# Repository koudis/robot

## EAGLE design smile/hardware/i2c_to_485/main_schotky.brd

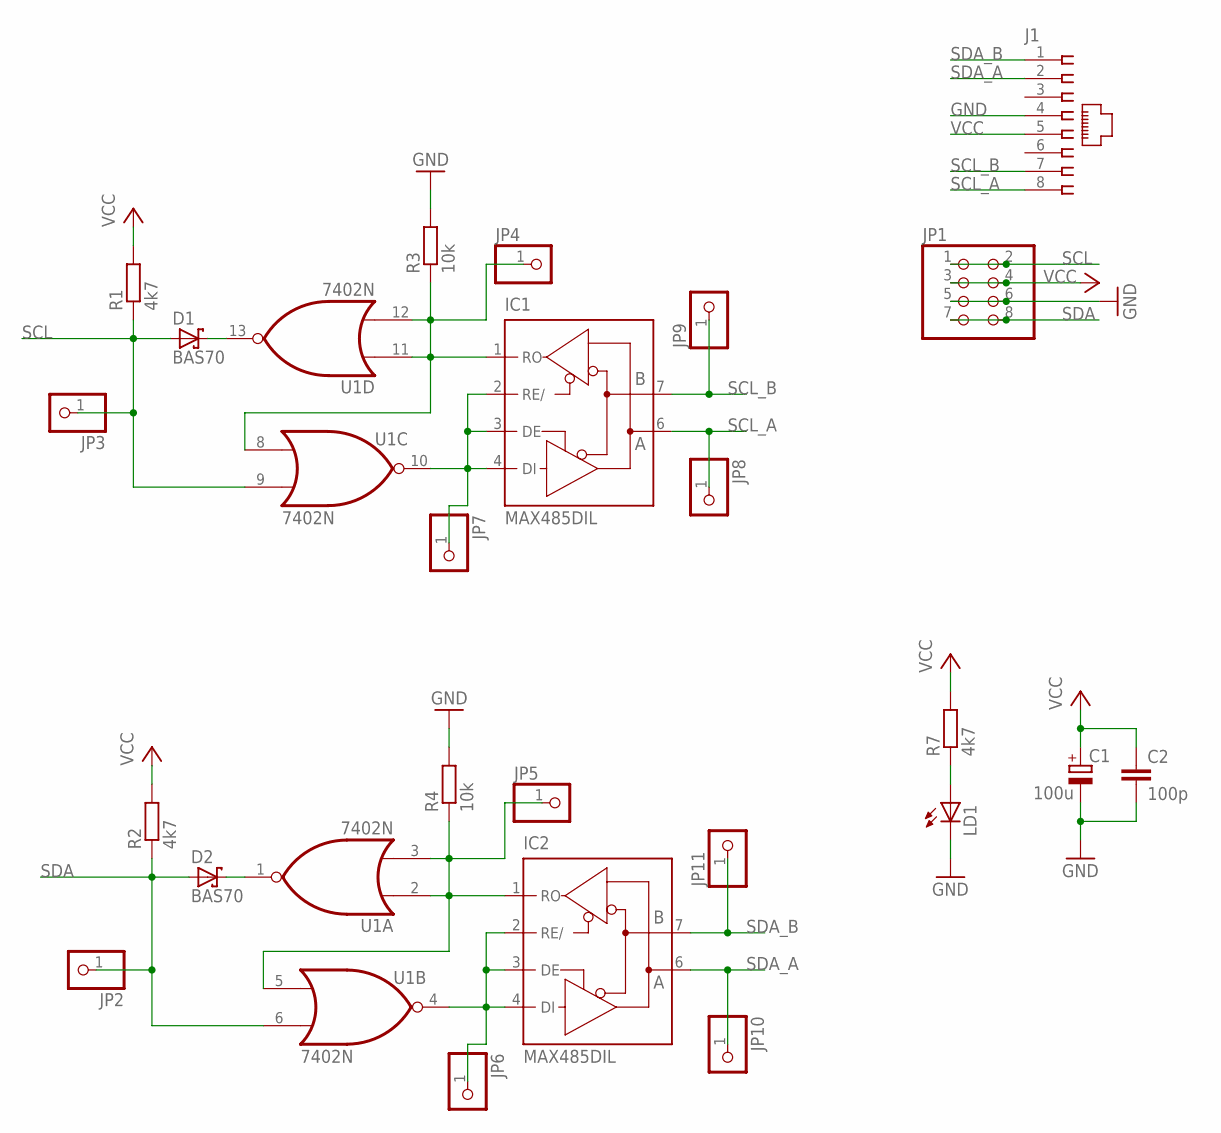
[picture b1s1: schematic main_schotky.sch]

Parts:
C1: 100u; E2-4
C2: 100p; C025-024X044
D1, D2: BAS70; SOT23
IC1, IC2: MAX485DIL; DIL08
J1: 215877-4
JP1: PINHD-2X4; 2X04
JP2, JP3, JP4, JP5, JP6, JP7, JP8, JP9, JP10, JP11: PINHD-1X1/LONG; 1X01
LD1: LEDSMT1206; 1206
R1, R2, R7: 4k7; R0805
R3, R4: 10k; R0805
U1: 7402N; DIL14

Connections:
GND: C1.-, C2.2, IC1.5 (GND), IC2.5 (GND), J1.4, JP1.5, JP1.6, LD1.C, R3.2, R4.2, U1.7 (GND)
unnamed: IC2.2 (RE/), IC2.3 (DE), IC2.4 (DI), JP6.1, U1.4 (O)
unnamed: IC2.1 (RO), JP5.1, R4.1, U1.2 (I0), U1.3 (I1), U1.5 (I0)
unnamed: D1.3 (C), U1.13 (O)
unnamed: D2.3 (C), U1.1 (O)
unnamed: LD1.A, R7.1
unnamed: IC1.2 (RE/), IC1.3 (DE), IC1.4 (DI), JP7.1, U1.10 (O)
unnamed: IC1.1 (RO), JP4.1, R3.1, U1.8 (I0), U1.11 (I0), U1.12 (I1)
SCL: D1.1 (A), JP1.1, JP1.2, JP3.1, R1.1, U1.9 (I1)
SCL_A: IC1.6 (A), J1.8, JP8.1
SCL_B: IC1.7 (B), J1.7, JP9.1
SDA: D2.1 (A), JP1.7, JP1.8, JP2.1, R2.1, U1.6 (I1)
SDA_A: IC2.6 (A), J1.2, JP10.1
SDA_B: IC2.7 (B), J1.1, JP11.1
VCC: C1.+, C2.1, IC1.8 (VCC), IC2.8 (VCC), J1.5, JP1.3, JP1.4, R1.2, R2.2, R7.2, U1.14 (VCC)

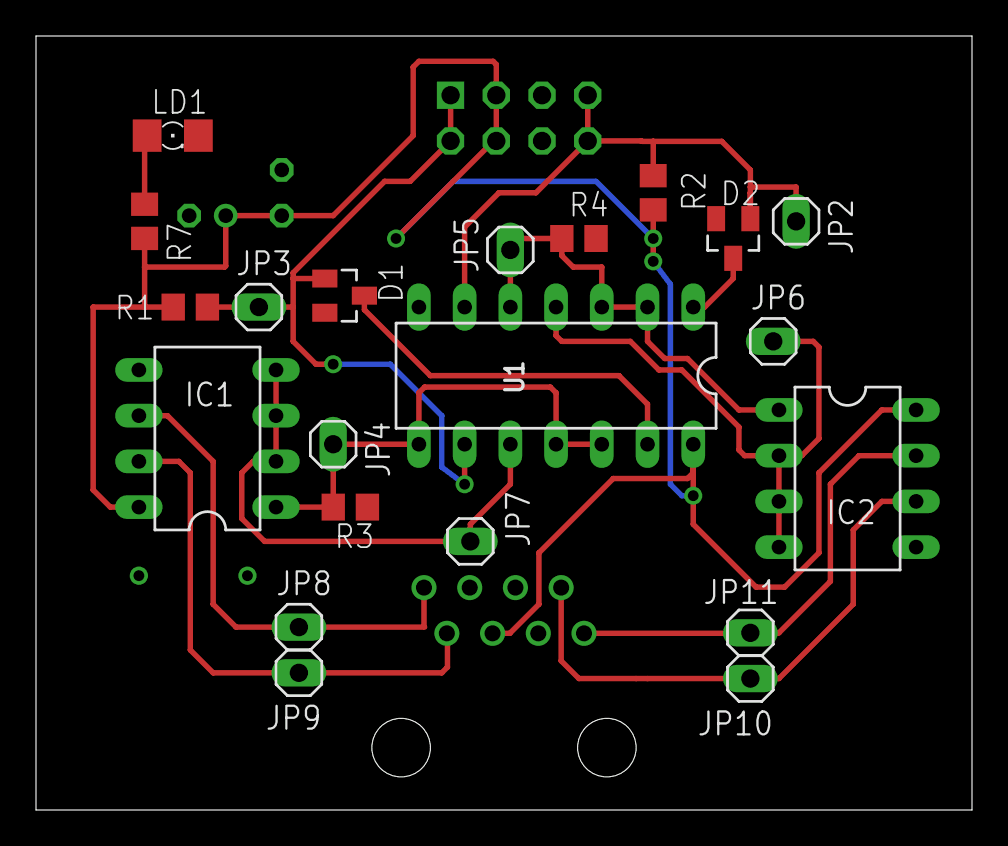
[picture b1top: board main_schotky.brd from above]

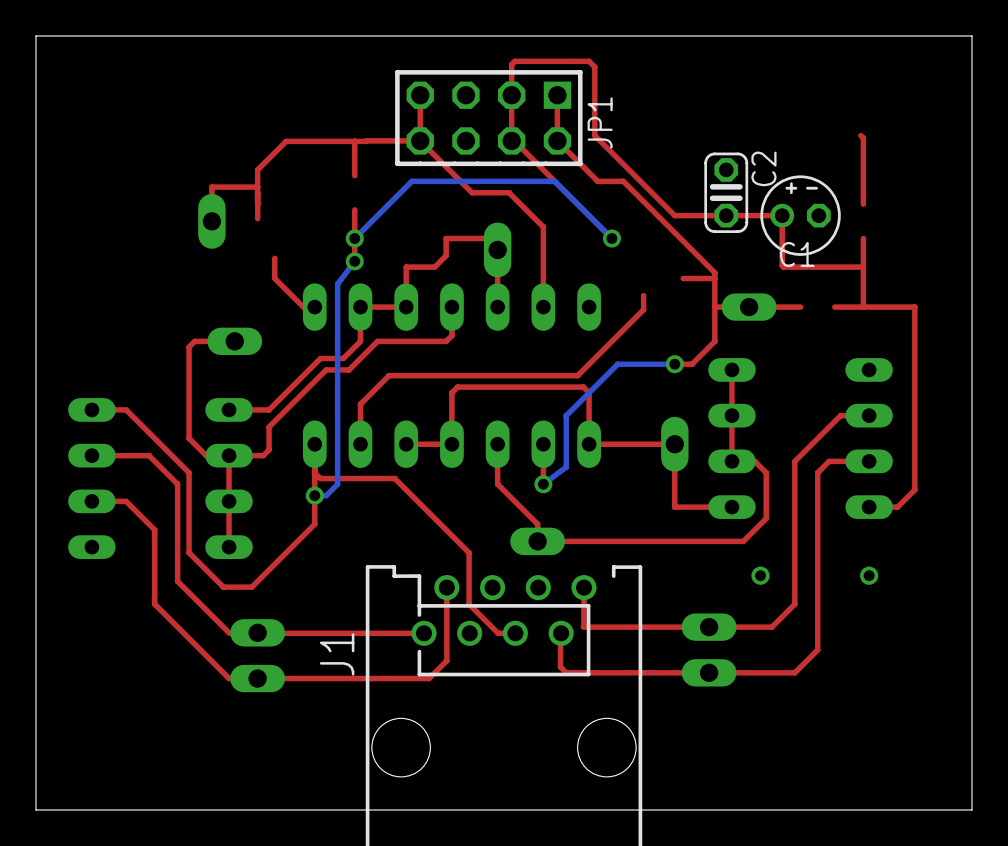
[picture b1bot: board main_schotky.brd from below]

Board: 2 copper layers, 52.0 x 43.0 mm, 25 parts (4 on the bottom side), 15 nets.

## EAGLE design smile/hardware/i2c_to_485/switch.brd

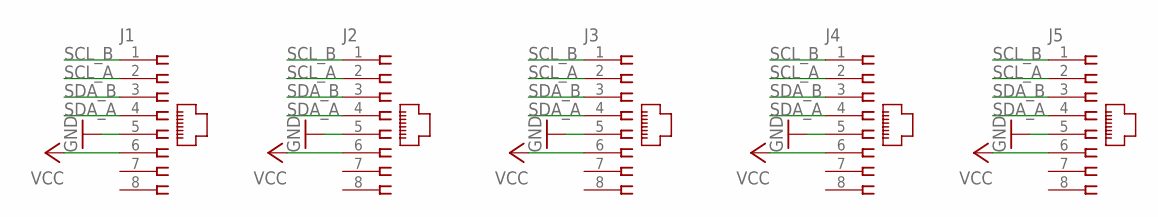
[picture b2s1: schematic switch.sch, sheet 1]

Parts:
J1, J2, J3, J4, J5: 215877-4

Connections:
GND: J1.5, J2.5, J3.5, J4.5, J5.5
SCL_A: J1.2, J2.2, J3.2, J4.2, J5.2
SCL_B: J1.1, J2.1, J3.1, J4.1, J5.1
SDA_A: J1.4, J2.4, J3.4, J4.4, J5.4
SDA_B: J1.3, J2.3, J3.3, J4.3, J5.3
VCC: J1.6, J2.6, J3.6, J4.6, J5.6

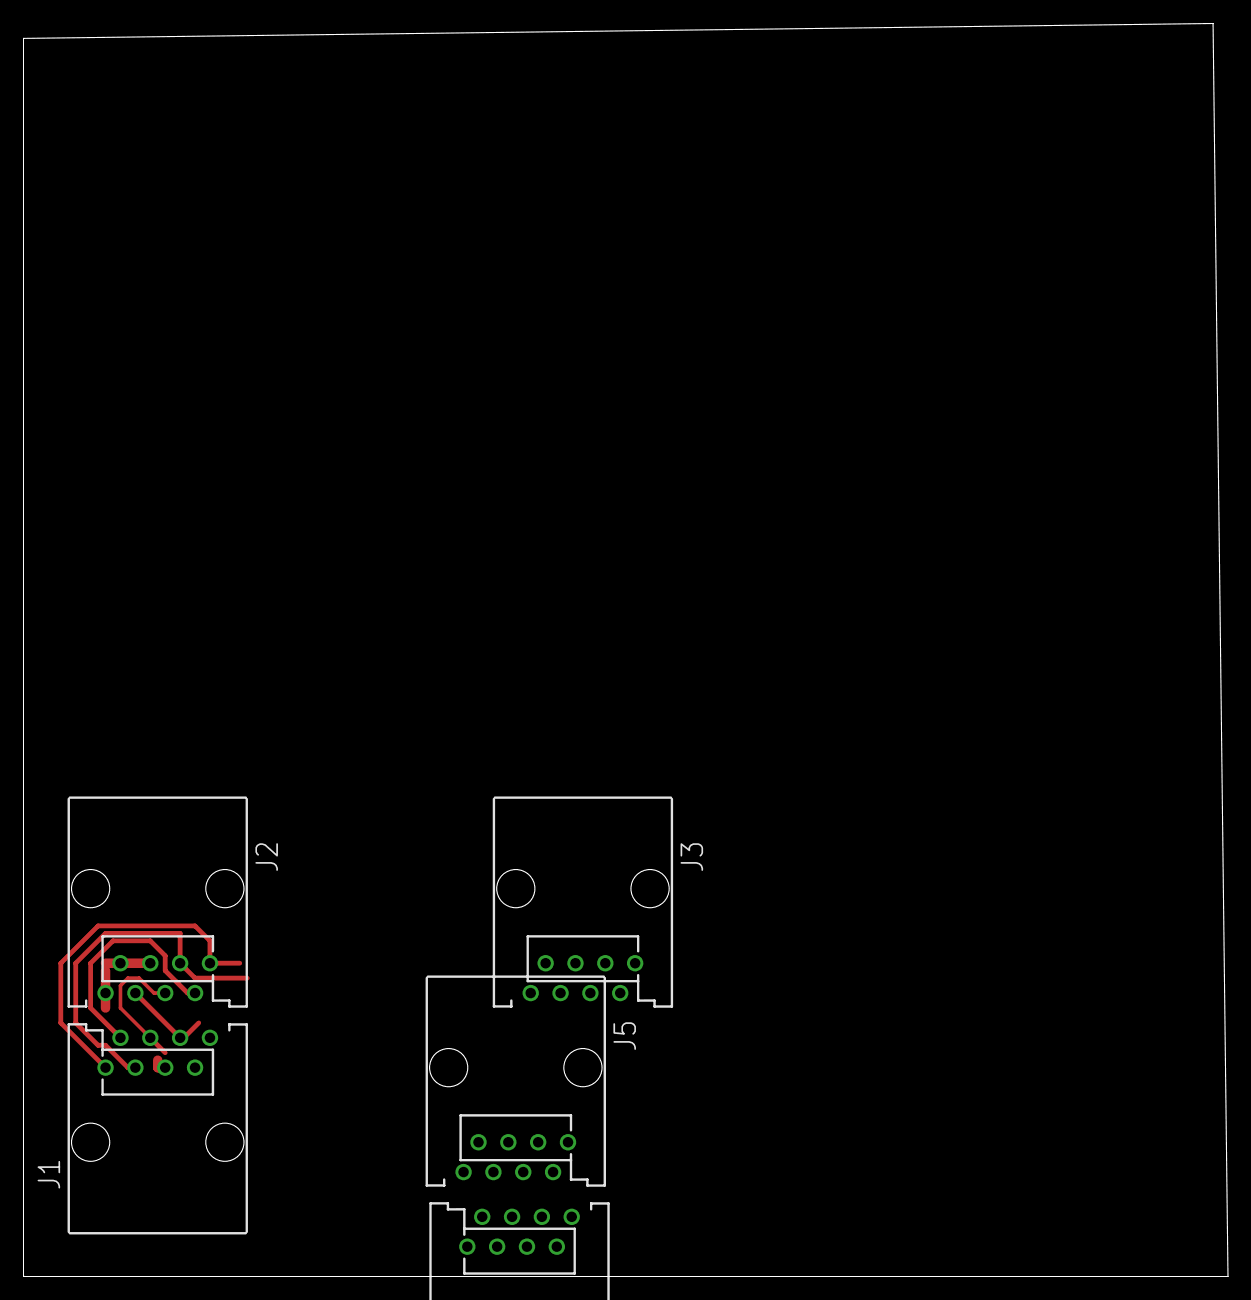
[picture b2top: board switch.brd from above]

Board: 2 copper layers, 102.5 x 106.7 mm, 5 parts (0 on the bottom side), 6 nets.

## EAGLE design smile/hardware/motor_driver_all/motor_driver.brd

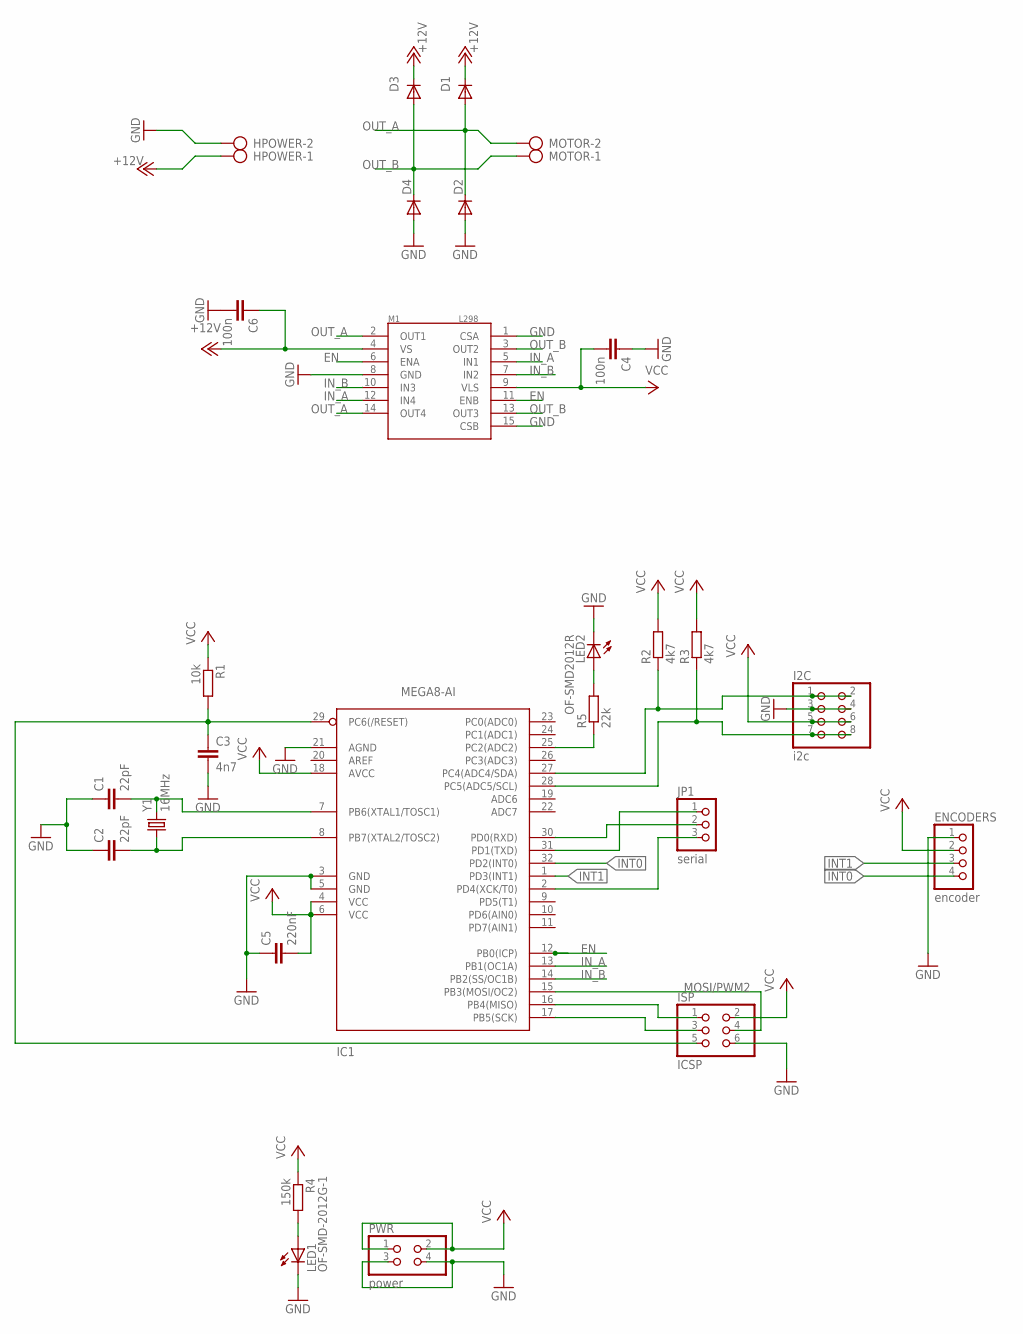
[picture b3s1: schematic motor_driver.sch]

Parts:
C1, C2: 22pF; C0805
C3: 4n7; 0805
C4: 100n; 0805
C5: 220nF; 0805
C6: 100n; C0805
D1, D2, D3, D4: DIODE-SMB; SMB
ENCODERS: encoder; 1X04-S
HPOWER: AK500/2
I2C: i2c; 2X04
IC1: MEGA8-AI; TQFP32-08
ISP: ICSP; 2X03
JP1: serial; 1X03-S
LED1: OF-SMD-2012G-1; CHIPLED_1206
LED2: OF-SMD2012R; CHIPLED_1206
M1: L298; MULTIWATT15
MOTOR: AK500/2
PWR: power; 2X02
R1: 10k; R0805
R2, R3: 4k7; R0805
R4: 150k; R0805
R5: 22k; R0805
Y1: 16MHz; HC49UP

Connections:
+12V: C6.1, D1.C, D3.C, HPOWER.1, M1.4 (VS)
EN: IC1.12 (PB0(ICP)), M1.6 (ENA), M1.11 (ENB)
GND: C1.1, C2.1, C3.2, C4.1, C5.1, C6.2, D2.A, D4.A, ENCODERS.1, HPOWER.2, I2C.3, I2C.4, IC1.3 (GND), IC1.5 (GND), IC1.21 (AGND), ISP.6, LED1.C, LED2.C, M1.1 (CSA), M1.8 (GND), M1.15 (CSB), PWR.3, PWR.4
INT0: ENCODERS.4, IC1.32 (PD2(INT0))
INT1: ENCODERS.3, IC1.1 (PD3(INT1))
IN_A: IC1.13 (PB1(OC1A)), M1.5 (IN1), M1.12 (IN4)
IN_B: IC1.14 (PB2(SS/OC1B)), M1.7 (IN2), M1.10 (IN3)
MISO: IC1.16 (PB4(MISO)), ISP.1
MOSI/PWM2: IC1.15 (PB3(MOSI/OC2)), ISP.4
unnamed: IC1.31 (PD1(TXD)), JP1.1
unnamed: C2.2, IC1.8 (PB7(XTAL2/TOSC2)), Y1.1
unnamed: C1.2, IC1.7 (PB6(XTAL1/TOSC1)), Y1.2
unnamed: IC1.30 (PD0(RXD)), JP1.2
unnamed: IC1.2 (PD4(XCK/T0)), JP1.3
unnamed: IC1.25 (PC2(ADC2)), R5.1
unnamed: LED1.A, R4.2
unnamed: LED2.A, R5.2
OUT_A: D1.A, D2.C, M1.2 (OUT1), M1.14 (OUT4), MOTOR.2
OUT_B: D3.A, D4.C, M1.3 (OUT2), M1.13 (OUT3), MOTOR.1
RESET: C3.1, IC1.29 (PC6(/RESET)), ISP.5, R1.2
SCK: IC1.17 (PB5(SCK)), ISP.3
SCL: I2C.7, I2C.8, IC1.28 (PC5(ADC5/SCL)), R3.1
SDA: I2C.1, I2C.2, IC1.27 (PC4(ADC4/SDA)), R2.1
VCC: C4.2, C5.2, ENCODERS.2, I2C.5, I2C.6, IC1.4 (VCC), IC1.6 (VCC), IC1.18 (AVCC), ISP.2, M1.9 (VLS), PWR.1, PWR.2, R1.1, R2.2, R3.2, R4.1

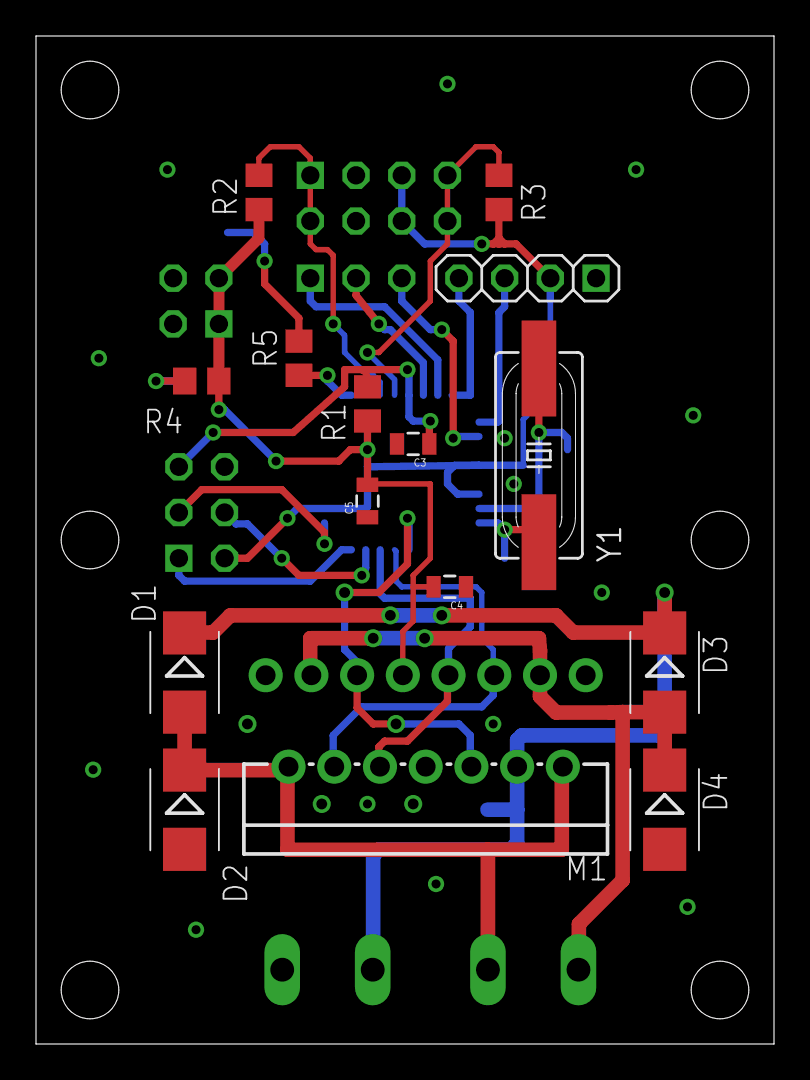
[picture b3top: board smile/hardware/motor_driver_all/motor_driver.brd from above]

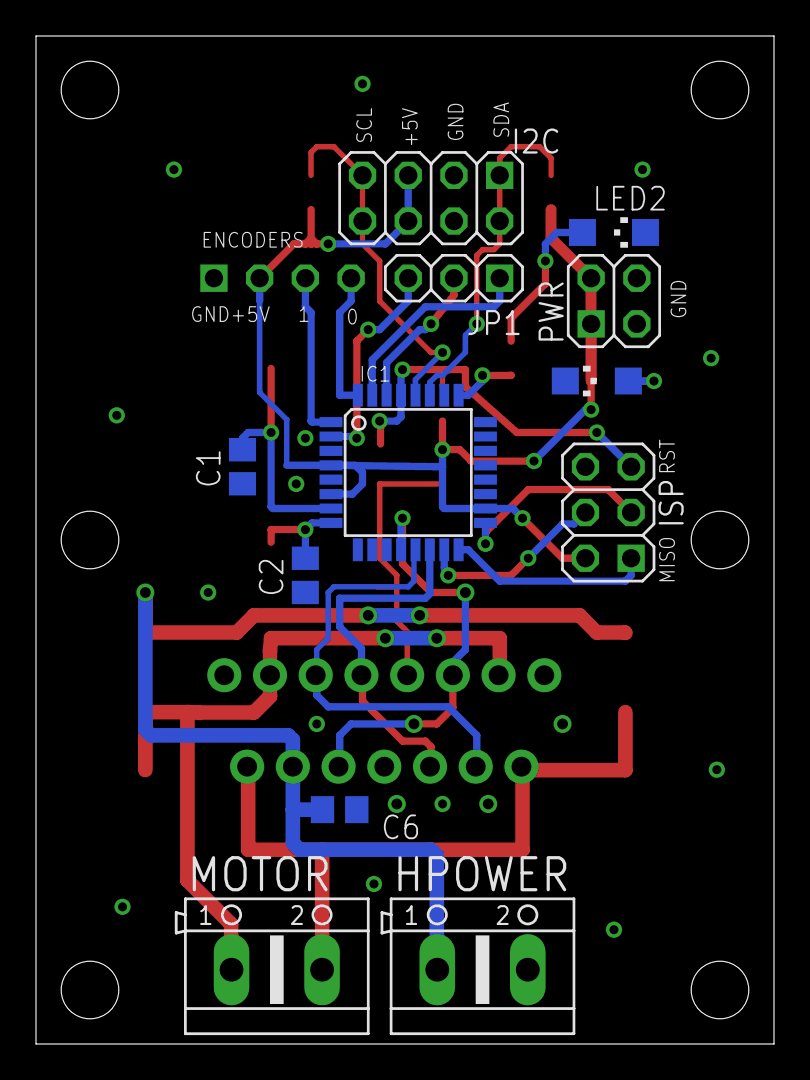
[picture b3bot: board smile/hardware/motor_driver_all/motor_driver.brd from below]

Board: 2 copper layers, 41.0 x 56.0 mm, 27 parts (12 on the bottom side), 24 nets.

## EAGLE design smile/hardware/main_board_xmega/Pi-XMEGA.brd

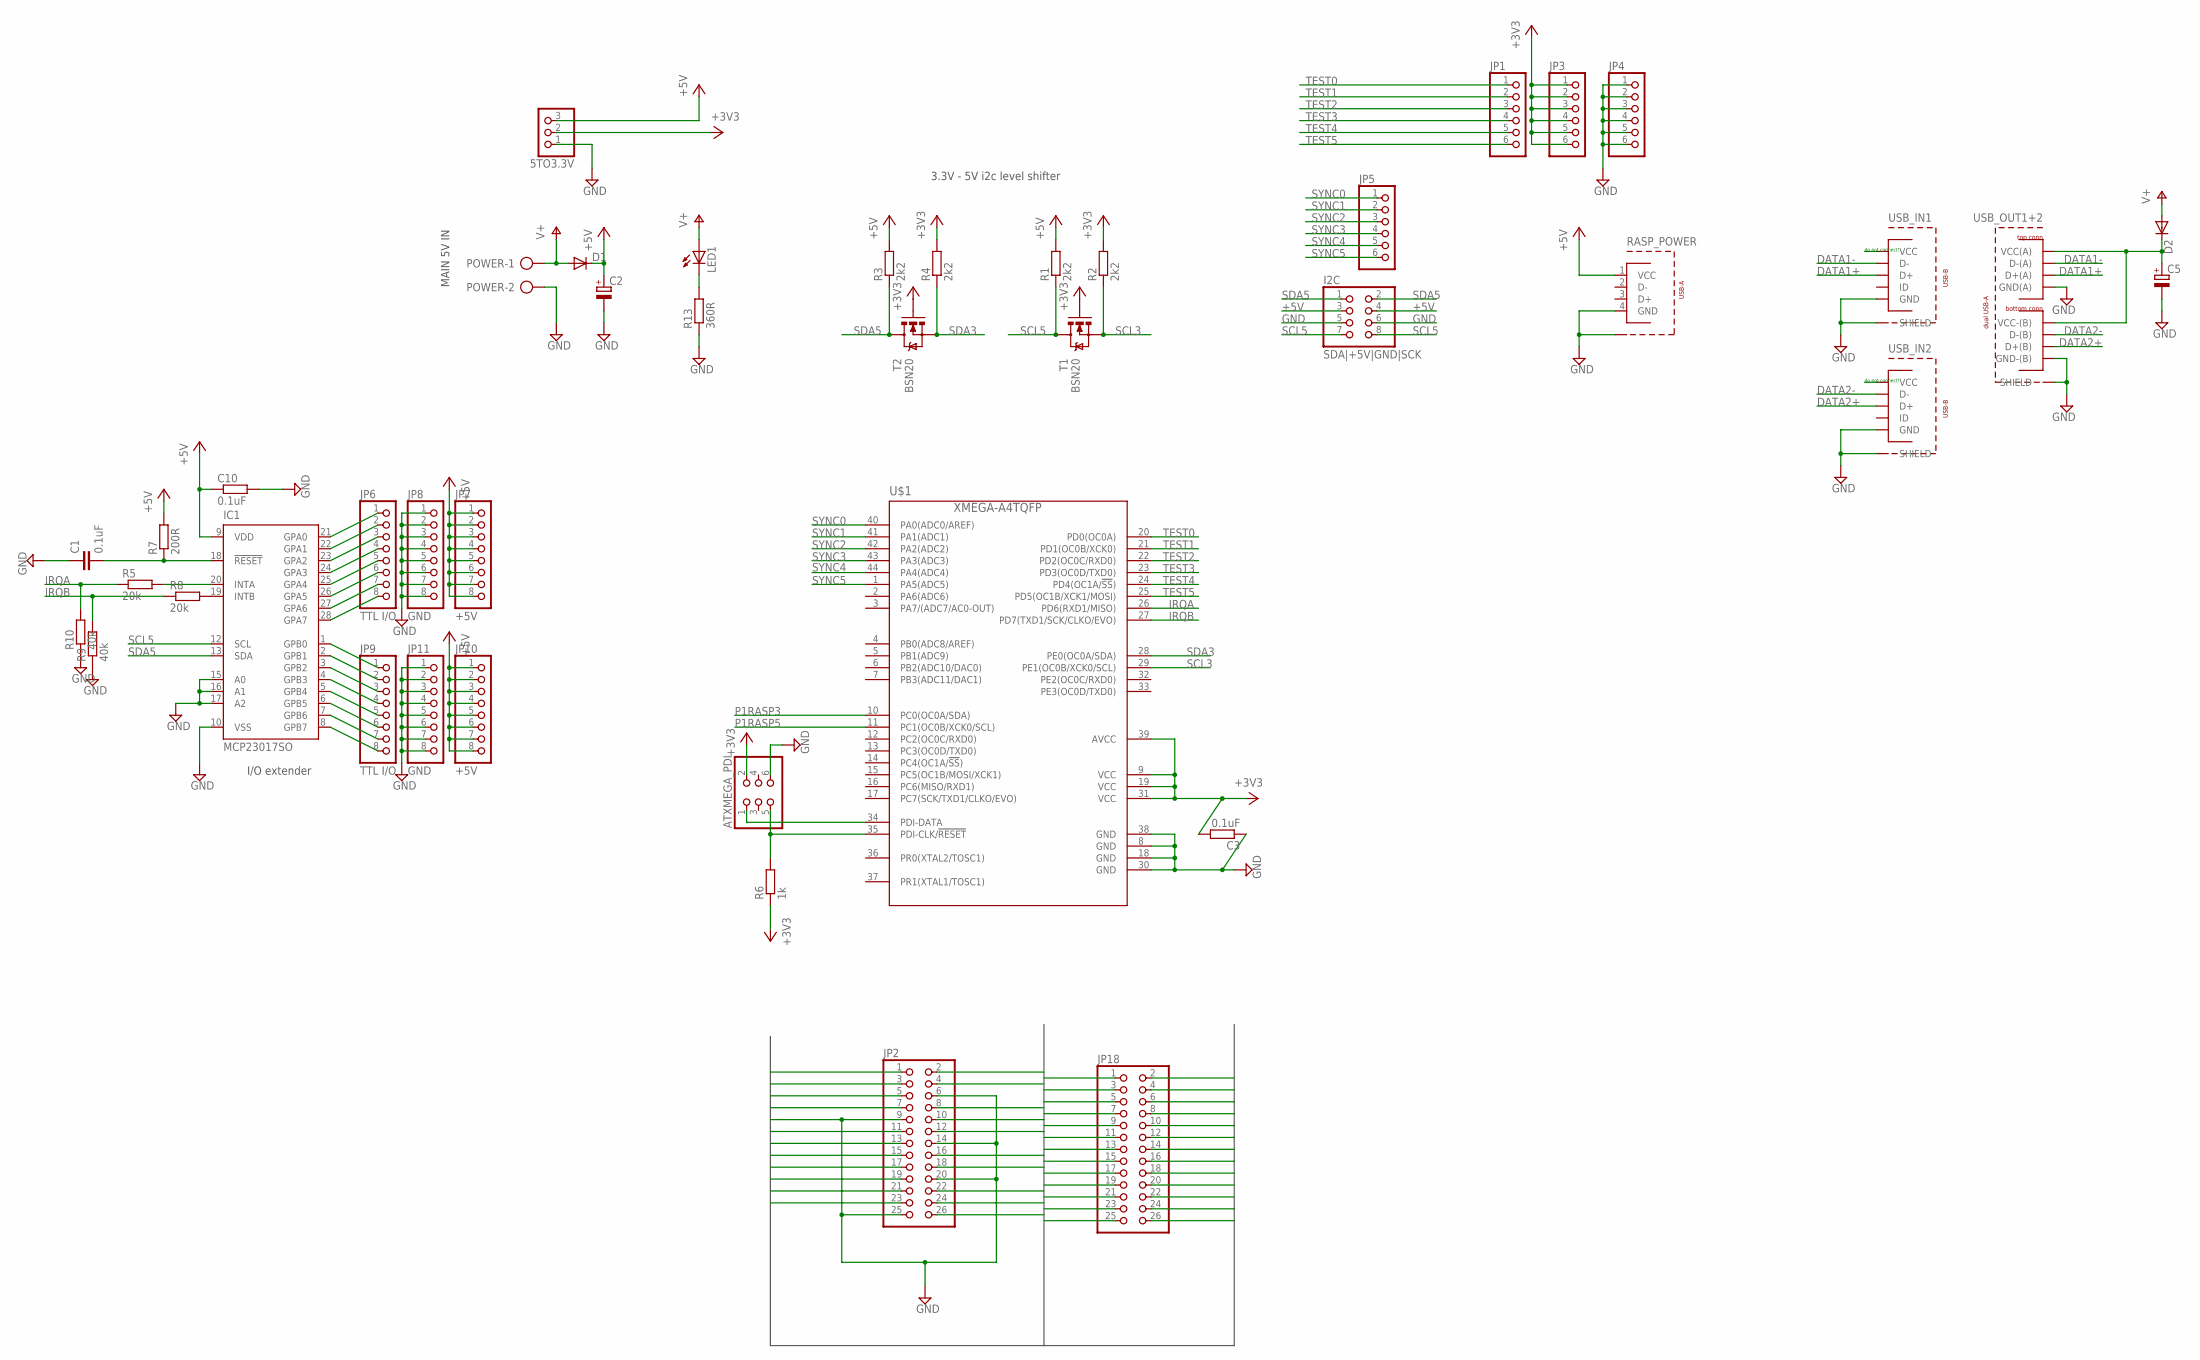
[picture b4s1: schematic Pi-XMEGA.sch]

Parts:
5TO3.3V: PINHD-1X3; 1X03
ATXMEGA_PDI: PINHD-2X03_2.54; 2X03
C1, C3, C10: 0.1uF; 0805BIG
C2, C5: CPOL-EUE5-8.5; E5-8,5
D1, D2: DIODE-C1702-05; C1702-05
I2C: SDA|+5V|GND|SCK; 2X04
IC1: MCP23017SO; SO28W
JP1, JP3, JP4, JP5: PINHD-1X06_2.54-S; 1X06-S
JP2, JP18: PINHD-2X13_2.54; 2X13
JP6, JP9: TTL I/O; 1X08-S
JP7, JP10: +5V; 1X08-S
JP8, JP11: GND; 1X08-S
LED1: LED3MM
POWER: AK500/2
R1, R2, R3, R4: 2k2; 0805BIG
R5, R8: 20k; 0805BIG
R6: 1k; 0805BIG
R7: 200R; 0805BIG
R9, R10: 40k; 0805BIG
R13: 360R; 0805BIG
RASP_POWER: USB-A
T1, T2: BSN20; SOT23
U$1: XMEGA-A4TQFP; TQFP44
USB_IN1, USB_IN2: USB-B-MICRO
USB_OUT1+2: DUAL-USB-A

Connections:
+3V3: 5TO3.3V.2, ATXMEGA_PDI.2, C3.2, JP3.1, JP3.2, JP3.3, JP3.4, JP3.5, JP3.6, R2.2, R4.2, R6.1, T1.1 (G), T2.1 (G), U$1.9 (VCC), U$1.19 (VCC), U$1.31 (VCC), U$1.39 (AVCC)
+5V: 5TO3.3V.3, C2.+, C10.1, D1.C, I2C.3, I2C.4, IC1.9 (VDD), JP7.1, JP7.2, JP7.3, JP7.4, JP7.5, JP7.6, JP7.7, JP7.8, JP10.1, JP10.2, JP10.3, JP10.4, JP10.5, JP10.6, JP10.7, JP10.8, R1.2, R3.2, R7.2, RASP_POWER.1 (VCC)
DATA1+: USB_IN1.3 (D+), USB_OUT1+2.3 (D+(A))
DATA1-: USB_IN1.2 (D-), USB_OUT1+2.2 (D-(A))
DATA2+: USB_IN2.3 (D+), USB_OUT1+2.7 (D+(B))
DATA2-: USB_IN2.2 (D-), USB_OUT1+2.6 (D-(B))
GND: 5TO3.3V.1, ATXMEGA_PDI.6, C1.1, C2.-, C3.1, C5.-, C10.2, I2C.5, I2C.6, IC1.10 (VSS), IC1.15 (A0), IC1.16 (A1), IC1.17 (A2), JP2.6, JP2.9, JP2.14, JP2.20, JP2.25, JP4.1, JP4.2, JP4.3, JP4.4, JP4.5, JP4.6, JP8.1, JP8.2, JP8.3, JP8.4, JP8.5, JP8.6, JP8.7, JP8.8, JP11.1, JP11.2, JP11.3, JP11.4, JP11.5, JP11.6, JP11.7, JP11.8, JP18.6, JP18.9, JP18.14, JP18.20, JP18.25, POWER.2, R9.1, R10.1, R13.1, RASP_POWER.4 (GND), RASP_POWER.S1 (SHIELD), RASP_POWER.S2 (SHIELD), U$1.8 (GND), U$1.18 (GND), U$1.30 (GND), U$1.38 (GND), USB_IN1.5 (GND), USB_IN1.S1 (SHIELD), USB_IN1.S2 (SHIELD), USB_IN2.5 (GND), USB_IN2.S1 (SHIELD), USB_IN2.S2 (SHIELD), USB_OUT1+2.4 (GND(A)), USB_OUT1+2.8 (GND-(B)), USB_OUT1+2.S1 (SHIELD), USB_OUT1+2.S2 (SHIELD), USB_OUT1+2.S3 (SHIELD), USB_OUT1+2.S4 (SHIELD)
IRQA: R5.1, R10.2, U$1.26 (PD6(RXD1/MISO))
IRQB: R8.1, R9.2, U$1.27 (PD7(TXD1/SCK/CLKO/EVO))
unnamed: IC1.20 (INTA), R5.2
unnamed: IC1.19 (INTB), R8.2
unnamed: IC1.21 (GPA0), JP6.1
unnamed: IC1.22 (GPA1), JP6.2
unnamed: ATXMEGA_PDI.5, R6.2, U$1.35 (PDI-CLK/!RESET)
unnamed: IC1.23 (GPA2), JP6.3
unnamed: IC1.24 (GPA3), JP6.4
unnamed: IC1.25 (GPA4), JP6.5
unnamed: C1.2, IC1.18 (!RESET), R7.1
unnamed: IC1.26 (GPA5), JP6.6
unnamed: IC1.27 (GPA6), JP6.7
unnamed: IC1.28 (GPA7), JP6.8
unnamed: IC1.1 (GPB0), JP9.1
unnamed: IC1.2 (GPB1), JP9.2
unnamed: IC1.3 (GPB2), JP9.3
unnamed: IC1.4 (GPB3), JP9.4
unnamed: IC1.5 (GPB4), JP9.5
unnamed: IC1.6 (GPB5), JP9.6
unnamed: IC1.7 (GPB6), JP9.7
unnamed: IC1.8 (GPB7), JP9.8
unnamed: ATXMEGA_PDI.1, U$1.34 (PDI-DATA)
unnamed: LED1.K (C), R13.2
N$FAKE1: USB_IN1.1 (VCC)
N$FAKE2: USB_IN2.1 (VCC)
P1RASP1: JP2.1, JP18.1
P1RASP2: JP2.2, JP18.2
P1RASP3: JP2.3, JP18.3, U$1.10 (PC0(OC0A/SDA))
P1RASP4: JP2.4, JP18.4
P1RASP5: JP2.5, JP18.5, U$1.11 (PC1(OC0B/XCK0/SCL))
P1RASP7: JP2.7, JP18.7
P1RASP8: JP2.8, JP18.8
P1RASP10: JP2.10, JP18.10
P1RASP11: JP2.11, JP18.11
P1RASP12: JP2.12, JP18.12
P1RASP13: JP2.13, JP18.13
P1RASP15: JP2.15, JP18.15
P1RASP16: JP2.16, JP18.16
P1RASP17: JP2.17, JP18.17
P1RASP18: JP2.18, JP18.18
P1RASP19: JP2.19, JP18.19
P1RASP21: JP2.21, JP18.21
P1RASP22: JP2.22, JP18.22
P1RASP23: JP2.23, JP18.23
P1RASP24: JP2.24, JP18.24
P1RASP26: JP2.26, JP18.26
SCL3: R2.1, T1.2 (S), U$1.29 (PE1(OC0B/XCK0/SCL))
SCL5: I2C.7, I2C.8, IC1.12 (SCL), R1.1, T1.3 (D)
SDA3: R4.1, T2.2 (S), U$1.28 (PE0(OC0A/SDA))
SDA5: I2C.1, I2C.2, IC1.13 (SDA), R3.1, T2.3 (D)
SYNC0: JP5.1, U$1.40 (PA0(ADC0/AREF))
SYNC1: JP5.2, U$1.41 (PA1(ADC1))
SYNC2: JP5.3, U$1.42 (PA2(ADC2))
SYNC3: JP5.4, U$1.43 (PA3(ADC3))
SYNC4: JP5.5, U$1.44 (PA4(ADC4))
SYNC5: JP5.6, U$1.1 (PA5(ADC5))
TEST0: JP1.1, U$1.20 (PD0(OC0A))
TEST1: JP1.2, U$1.21 (PD1(OC0B/XCK0))
TEST2: JP1.3, U$1.22 (PD2(OC0C/RXD0))
TEST3: JP1.4, U$1.23 (PD3(OC0D/TXD0))
TEST4: JP1.5, U$1.24 (PD4(OC1A/!SS!))
TEST5: JP1.6, U$1.25 (PD5(OC1B/XCK1/MOSI))
USB+5V: C5.+, D2.C, USB_OUT1+2.1 (VCC(A)), USB_OUT1+2.5 (VCC-(B))
V+: D1.A, D2.A, LED1.A, POWER.1

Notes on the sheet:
MAIN 5V IN
3.3V - 5V i2c level shifter
I/O extender
do not connect!

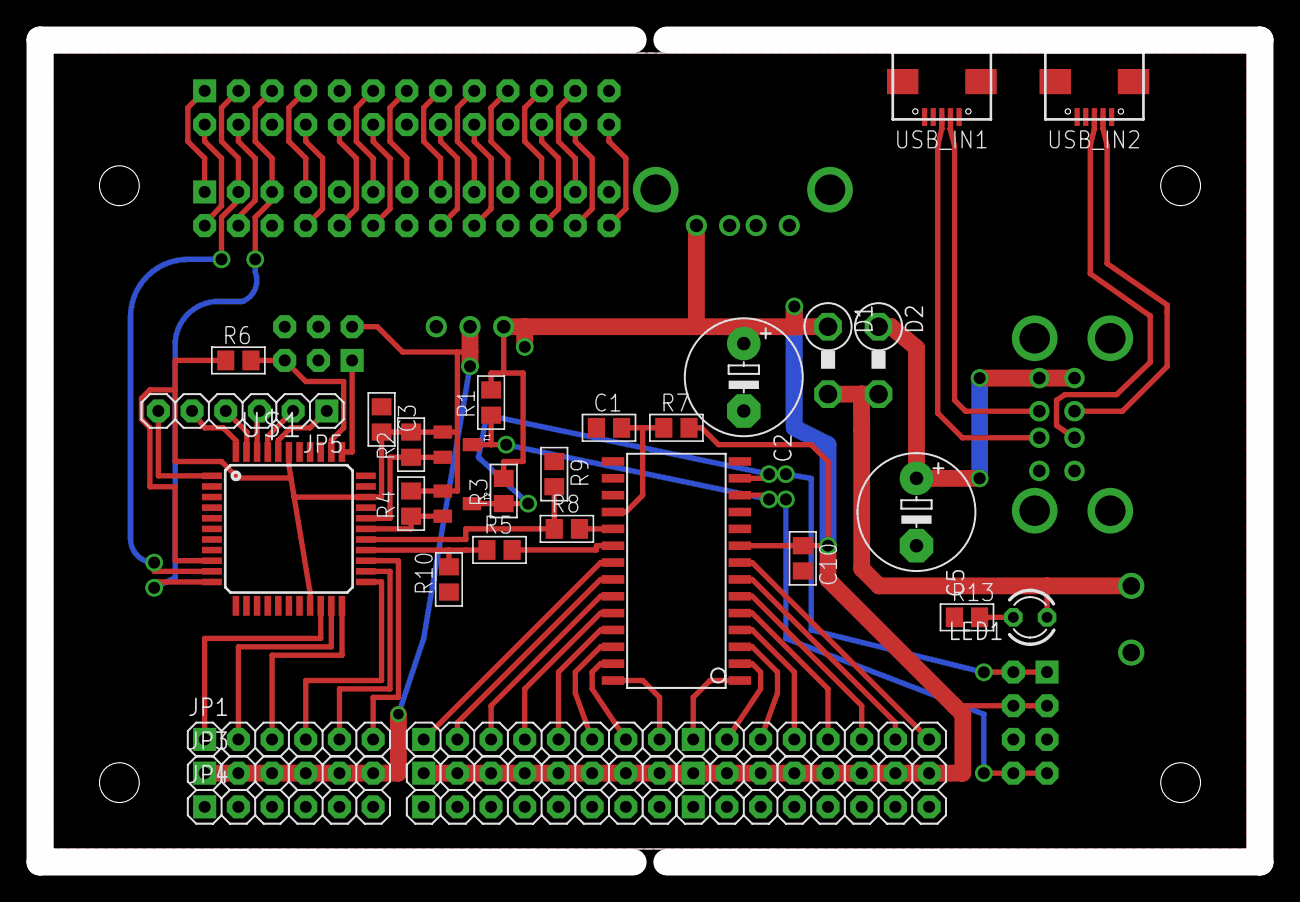
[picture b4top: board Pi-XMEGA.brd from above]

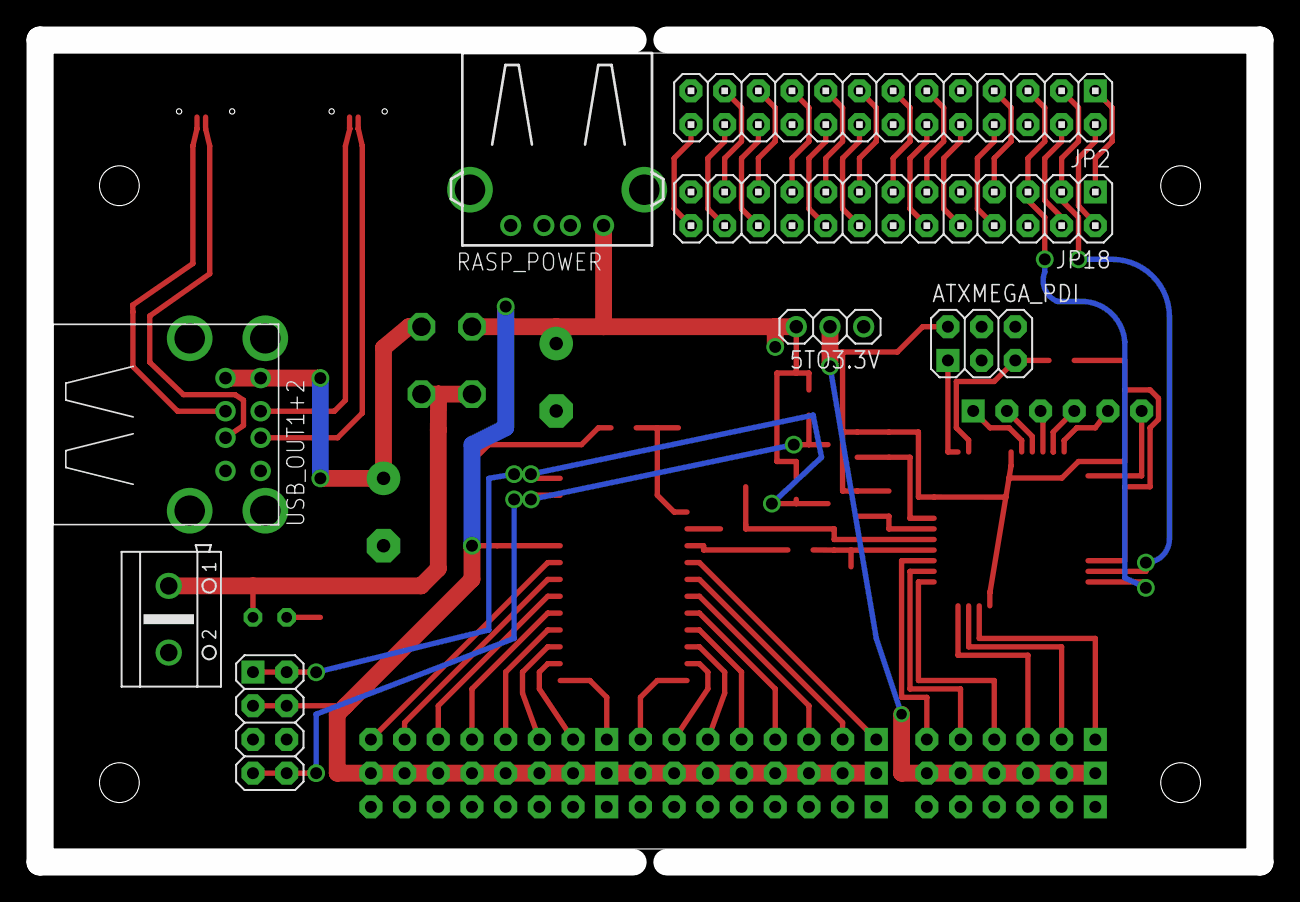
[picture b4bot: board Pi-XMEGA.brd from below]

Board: 2 copper layers, 92.0 x 62.0 mm, 43 parts (8 on the bottom side), 70 nets.

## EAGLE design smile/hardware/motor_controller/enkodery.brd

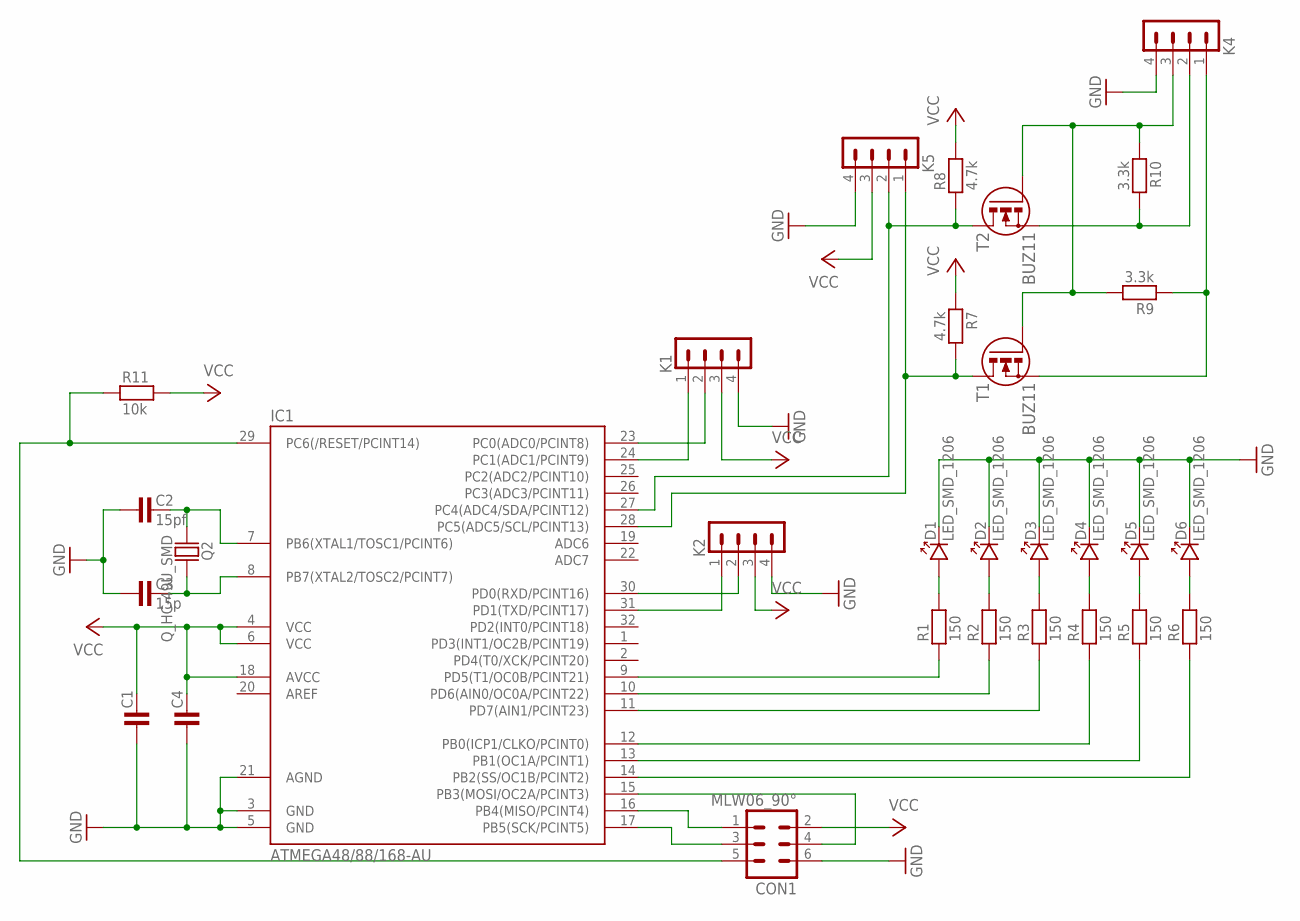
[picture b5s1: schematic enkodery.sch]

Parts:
C1, C4: C-KERAMIK_SMD_1206; 1206
C2: 15pf; 1206
C3: 15p; 1206
CON1: MLW06_90°; MLW06A
D1, D2, D3, D4, D5, D6: LED_SMD_1206; P1206
IC1: ATMEGA48/88/168-AU; TQFP32-08
K1, K2, K4, K5: PSH02-04W
Q2: Q_HC-49U_SMD; HC-49US
R1, R2, R3, R4, R5, R6: 150; 1206
R7, R8: 4.7k; 1206
R9, R10: 3.3k; 1206
R11: 10k; 1206
T1, T2: BUZ11; SOT23

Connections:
GND: C1.1, C2.1, C3.1, C4.1, CON1.6, D1.K, D2.K, D3.K, D4.K, D5.K, D6.K, IC1.3 (GND), IC1.5 (GND), IC1.21 (AGND), K1.4, K2.4, K4.4, K5.4
unnamed: IC1.30 (PD0(RXD/PCINT16)), K2.2
unnamed: IC1.31 (PD1(TXD/PCINT17)), K2.1
unnamed: IC1.23 (PC0(ADC0/PCINT8)), K1.2
unnamed: IC1.24 (PC1(ADC1/PCINT9)), K1.1
unnamed: C3.2, IC1.8 (PB7(XTAL2/TOSC2/PCINT7)), Q2.2
unnamed: CON1.1, IC1.16 (PB4(MISO/PCINT4))
unnamed: CON1.3, IC1.17 (PB5(SCK/PCINT5))
unnamed: CON1.4, IC1.15 (PB3(MOSI/OC2A/PCINT3))
unnamed: IC1.9 (PD5(T1/OC0B/PCINT21)), R1.1
unnamed: IC1.10 (PD6(AIN0/OC0A/PCINT22)), R2.1
unnamed: IC1.11 (PD7(AIN1/PCINT23)), R3.1
unnamed: IC1.12 (PB0(ICP1/CLKO/PCINT0)), R4.1
unnamed: IC1.13 (PB1(OC1A/PCINT1)), R5.1
unnamed: IC1.14 (PB2(SS/OC1B/PCINT2)), R6.1
unnamed: D1.A, R1.2
unnamed: D6.A, R6.2
unnamed: D5.A, R5.2
unnamed: D4.A, R4.2
unnamed: D3.A, R3.2
unnamed: D2.A, R2.2
unnamed: C2.2, IC1.7 (PB6(XTAL1/TOSC1/PCINT6)), Q2.1
unnamed: K4.3, R9.2, R10.1, T1.1 (G), T2.1 (G)
RST: CON1.5, IC1.29 (PC6(/RESET/PCINT14)), R11.1
SCL3: K4.1, R9.1, T1.2 (S)
SCL5: IC1.28 (PC5(ADC5/SCL/PCINT13)), K5.1, R7.2, T1.3 (D)
SDA3: K4.2, R10.2, T2.2 (S)
SDA5: IC1.27 (PC4(ADC4/SDA/PCINT12)), K5.2, R8.1, T2.3 (D)
VCC: C1.2, C4.2, CON1.2, IC1.4 (VCC), IC1.6 (VCC), IC1.18 (AVCC), K1.3, K2.3, K5.3, R7.1, R8.2, R11.2

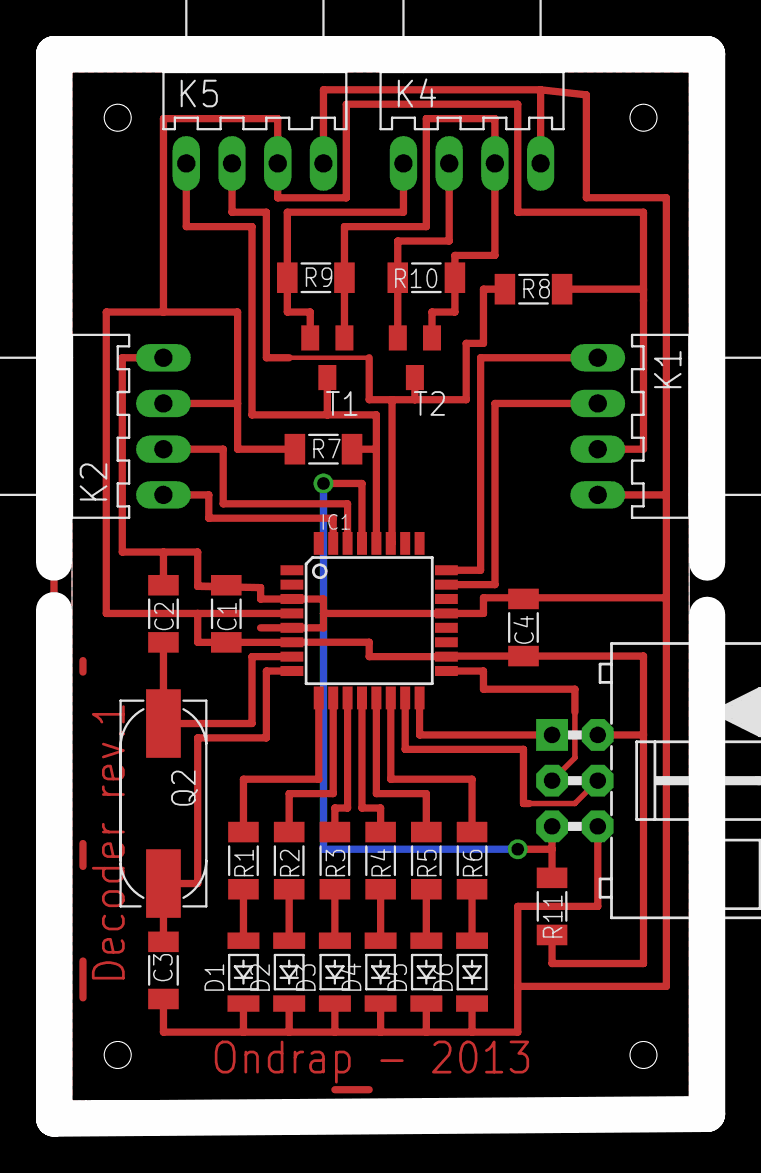
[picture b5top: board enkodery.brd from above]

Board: 2 copper layers, 36.3 x 59.1 mm, 30 parts (0 on the bottom side), 29 nets.

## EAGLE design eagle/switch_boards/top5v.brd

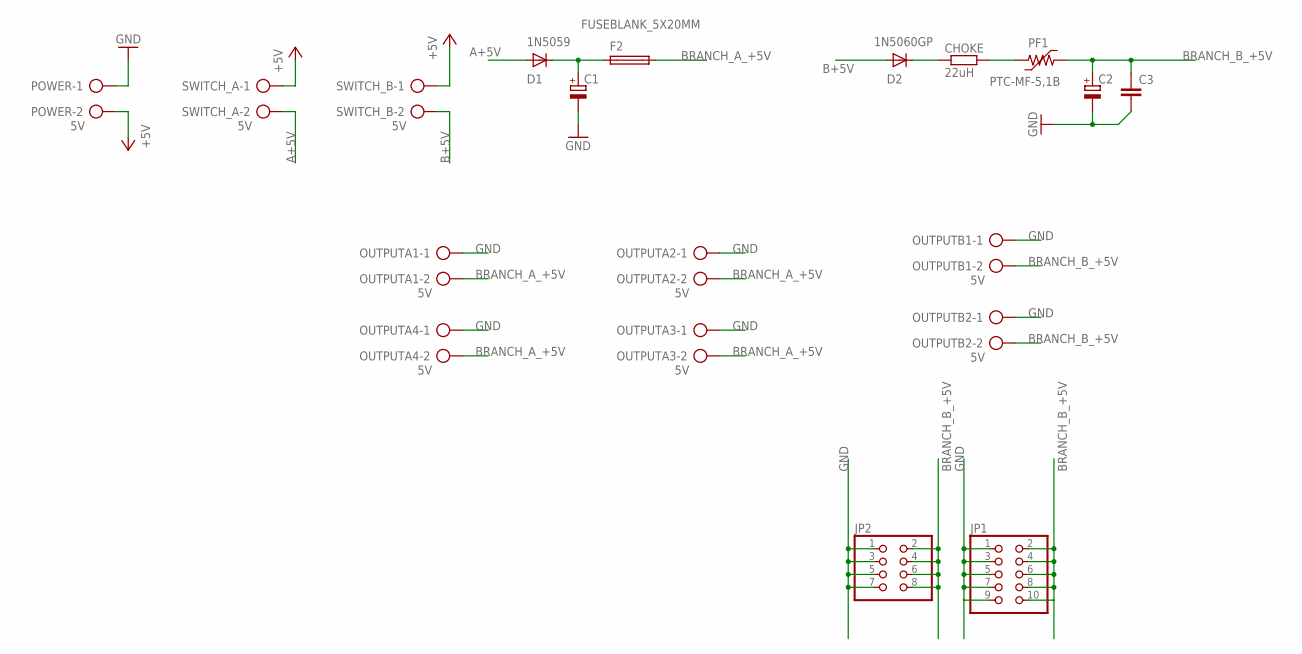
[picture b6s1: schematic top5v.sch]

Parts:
C1, C2: CPOL-EUE2.5-5; E2,5-5
C3: C-EU025-024X044; C025-024X044
CHOKE: 22uH; 0411/15
D1: 1N5059; DO204-10
D2: 1N5060GP; DO15-12
F2: FUSEBLANK_5X20MM; FUSE_HOLDER_5X20MM
JP1: PINHD-2X5; 2X05
JP2: PINHD-2X4; 2X04
OUTPUTA1, OUTPUTA2, OUTPUTA3, OUTPUTA4: 5V; AK500/2
OUTPUTB1, OUTPUTB2: 5V; AK500/2
PF1: PTC-MF-5,1B; MF-5/1B
POWER: 5V; AK500/2
SWITCH_A: 5V; AK500/2
SWITCH_B: 5V; AK500/2

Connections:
+5V: POWER.2, SWITCH_A.1, SWITCH_B.1
A+5V: D1.A, SWITCH_A.2
B+5V: D2.A, SWITCH_B.2
BRANCH_A_+5V: F2.1, OUTPUTA1.2, OUTPUTA2.2, OUTPUTA3.2, OUTPUTA4.2
BRANCH_B_+5V: C2.+, C3.1, JP1.2, JP1.4, JP1.6, JP1.8, JP1.10, JP2.2, JP2.4, JP2.6, JP2.8, OUTPUTB1.2, OUTPUTB2.2, PF1.2
GND: C1.-, C2.-, C3.2, JP1.1, JP1.3, JP1.5, JP1.7, JP1.9, JP2.1, JP2.3, JP2.5, JP2.7, OUTPUTA1.1, OUTPUTA2.1, OUTPUTA3.1, OUTPUTA4.1, OUTPUTB1.1, OUTPUTB2.1, POWER.1
unnamed: CHOKE.1, D2.C
unnamed: CHOKE.2, PF1.1
unnamed: C1.+, D1.C, F2.2

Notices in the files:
parts and their libraries:
SparkFun-Capacitors: Licensing: Creative Commons ShareAlike 4.0 International - https://creativecommons.org/licenses/by-sa/4.0
polyswitch: Copyright (C) 2008, Bob Starr
Copyright (C) PaJa 2011
Copyright (C) PaJa 2001-2011
